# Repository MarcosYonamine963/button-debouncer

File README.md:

# Four Debounced Buttons

The designed board has four debounced tactile buttons.

The board has an 6-pin socket header, containing the VCC, GND and the four output signals (Q1 to Q4).

Also, there are two auxiliary 2-pin header with VCC and GND, as you can see on the figure below.

The logic output of the Buttons 1 and 2 (Q1 and Q2) are NL (normally LOW). For the Buttons 3 and 4, user can configure to NL or NH by the sliding switch (SW5 and SW6).

## Schematics

It was used an quad OR gate to buffer the signal to the LED indicators.

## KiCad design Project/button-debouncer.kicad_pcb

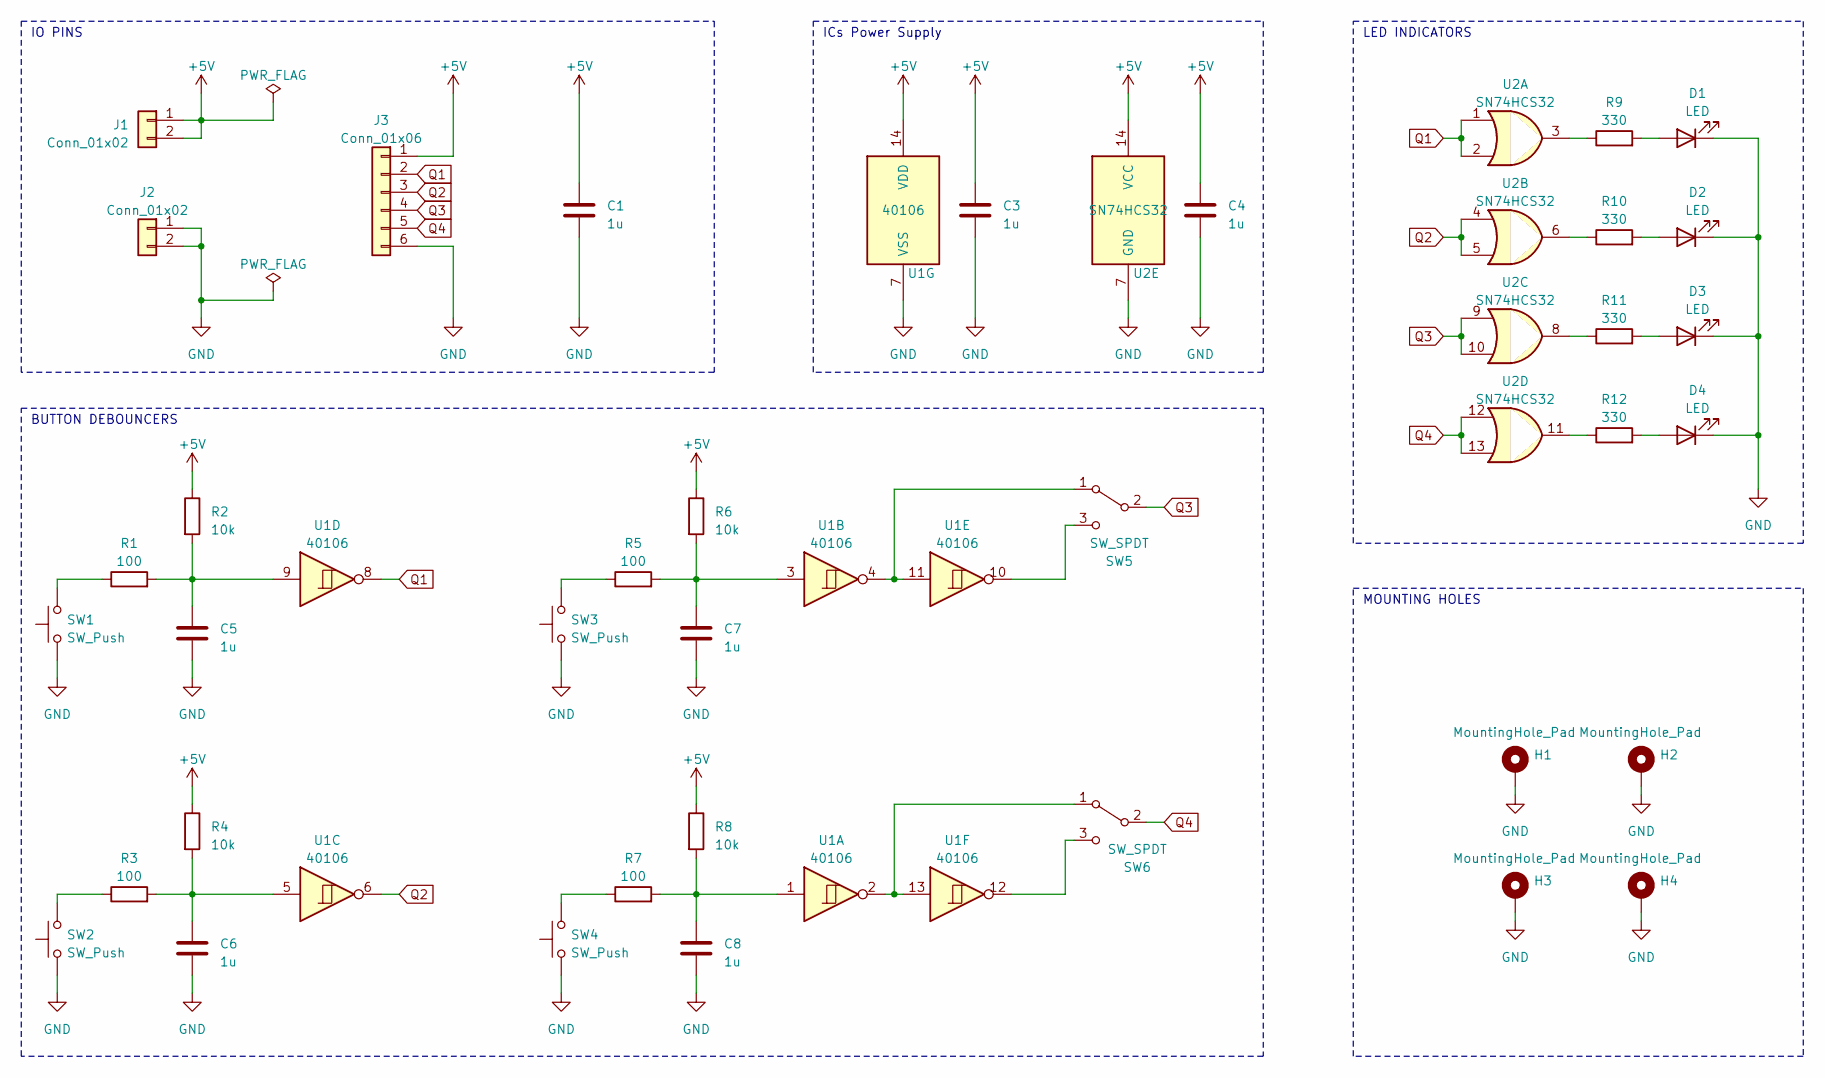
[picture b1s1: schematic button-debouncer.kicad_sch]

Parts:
C1: 1u; CP_Elec_4x4.5
C3, C4: 1u; C_0805_2012Metric
C5, C6, C7, C8: 1u; C_0402_1005Metric
D1, D2, D3, D4: LED; LED_0402_1005Metric
H1, H2, H3, H4: MountingHole_Pad; MountingHole_2.5mm_Pad
J1, J2: Conn_01x02; PinHeader_1x02_P2.54mm_Vertical
J3: Conn_01x06; PinSocket_1x06_P2.54mm_Vertical
R1, R3, R5, R7: 100; R_0402_1005Metric
R2, R4, R6, R8: 10k; R_0402_1005Metric
R9, R10, R11, R12: 330; R_0402_1005Metric
SW1, SW2, SW3, SW4: SW_Push; SW_PUSH_6mm
SW5, SW6: SW_SPDT; SW_Slide_1P2T_CK_OS102011MS2Q
U1: 40106; SOIC-14_3.9x8.7mm_P1.27mm
U2: SN74HCS32; SOIC-14_3.9x8.7mm_P1.27mm

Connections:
+5V: C1.1, C3.1, C4.1, J1.1, J1.2, J3.1, R2.1, R4.1, R6.1, R8.1, U1.14 (VDD), U2.14 (VCC)
GND: C1.2, C3.2, C4.2, C5.2, C6.2, C7.2, C8.2, D1.1 (K), D2.1 (K), D3.1 (K), D4.1 (K), H1.1, H2.1, H3.1, H4.1, J2.1, J2.2, J3.6, SW1.1, SW2.1, SW3.1, SW4.1, U1.7 (VSS), U2.7 (GND)
unnamed: C5.1, R1.2, R2.2, U1.9
unnamed: C6.1, R3.2, R4.2, U1.5
unnamed: C7.1, R5.2, R6.2, U1.3
unnamed: C8.1, R7.2, R8.2, U1.1
unnamed: D1.2 (A), R9.2
unnamed: D2.2 (A), R10.2
unnamed: D3.2 (A), R11.2
unnamed: D4.2 (A), R12.2
unnamed: R1.1, SW1.2
unnamed: R3.1, SW2.2
unnamed: R5.1, SW3.2
unnamed: R7.1, SW4.2
unnamed: R9.1, U2.3
unnamed: R10.1, U2.6
unnamed: R11.1, U2.8
unnamed: R12.1, U2.11
unnamed: SW5.1 (A), U1.4, U1.11
unnamed: SW5.3 (C), U1.10
unnamed: SW6.1 (A), U1.2, U1.13
unnamed: SW6.3 (C), U1.12
Q1: J3.2, U1.8, U2.1, U2.2
Q2: J3.3, U1.6, U2.4, U2.5
Q3: J3.4, SW5.2 (B), U2.9, U2.10
Q4: J3.5, SW6.2 (B), U2.12, U2.13

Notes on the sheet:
BUTTON DEBOUNCERS
ICs Power Supply
MOUNTING HOLES
IO PINS
LED INDICATORS

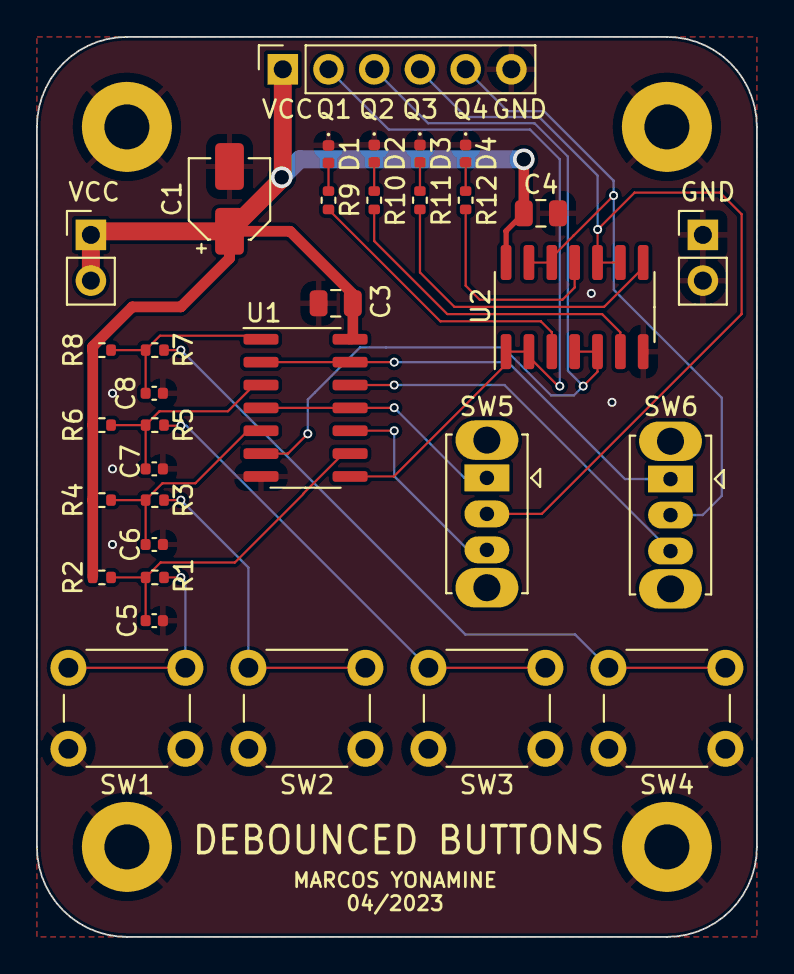
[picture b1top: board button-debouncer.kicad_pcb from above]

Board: 2 copper layers, 40.0 x 50.0 mm, 38 parts (0 on the bottom side), 26 nets.

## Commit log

2023-04-06 started new blank kiCad project
2023-04-06 updated .gitignore file
2023-04-06 updated blank project files location
2023-04-07 schematics done
2023-04-07 fixed power flags
2023-04-07 added footprints to components
2023-04-07 Finished PCB layout
2023-04-07 updated resistors values
2023-04-08 project in stable version - production ordered
2023-04-08 added schematics in .png file
2023-04-08 updated gerber Drill files
2023-04-08 generated gerber zip file
